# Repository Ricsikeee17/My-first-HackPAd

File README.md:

# SWITCHY

So this is my first ever project that gets a Github repository.

6 mechanical switches for macros

1 dedicated mode switch

Rotary encoder

OLED display for mode/status feedback

USB HID keyboard emulation

Built using Seeded XIAO RP2040.

## Features

Multiple macro modes (Mode 1 / Mode 2 / etc.)

OLED display shows:

Current mode

Encoder status

Custom labels (optional)

Rotary encoder:

Volume control

Fully programmable macros

## PCB

Here's a screenshot of the schematic:

The PCB:

## CAD Model
The case is made out 3 parts and it just only has parts that you could print.
It fits together using 4 M3 heatset inserts and bolts.

## BOM:
Here should be everything you need to make this hackpad

- 7x MX Switches
- 4x DSA Keycaps
- 4x M3x5x4 Heatset inserts
- 4x M3x16mm SHCS Bolts
- 7x 1N4148 DO-35 Diodes.
- 3x SK6812 MINI-E LEDs
- 1x 0.91" 128x32 OLED Display
- 1x EC11 Rotary Encoder
- 1x XIAO RP2040
- 1x Case (3 printed parts)

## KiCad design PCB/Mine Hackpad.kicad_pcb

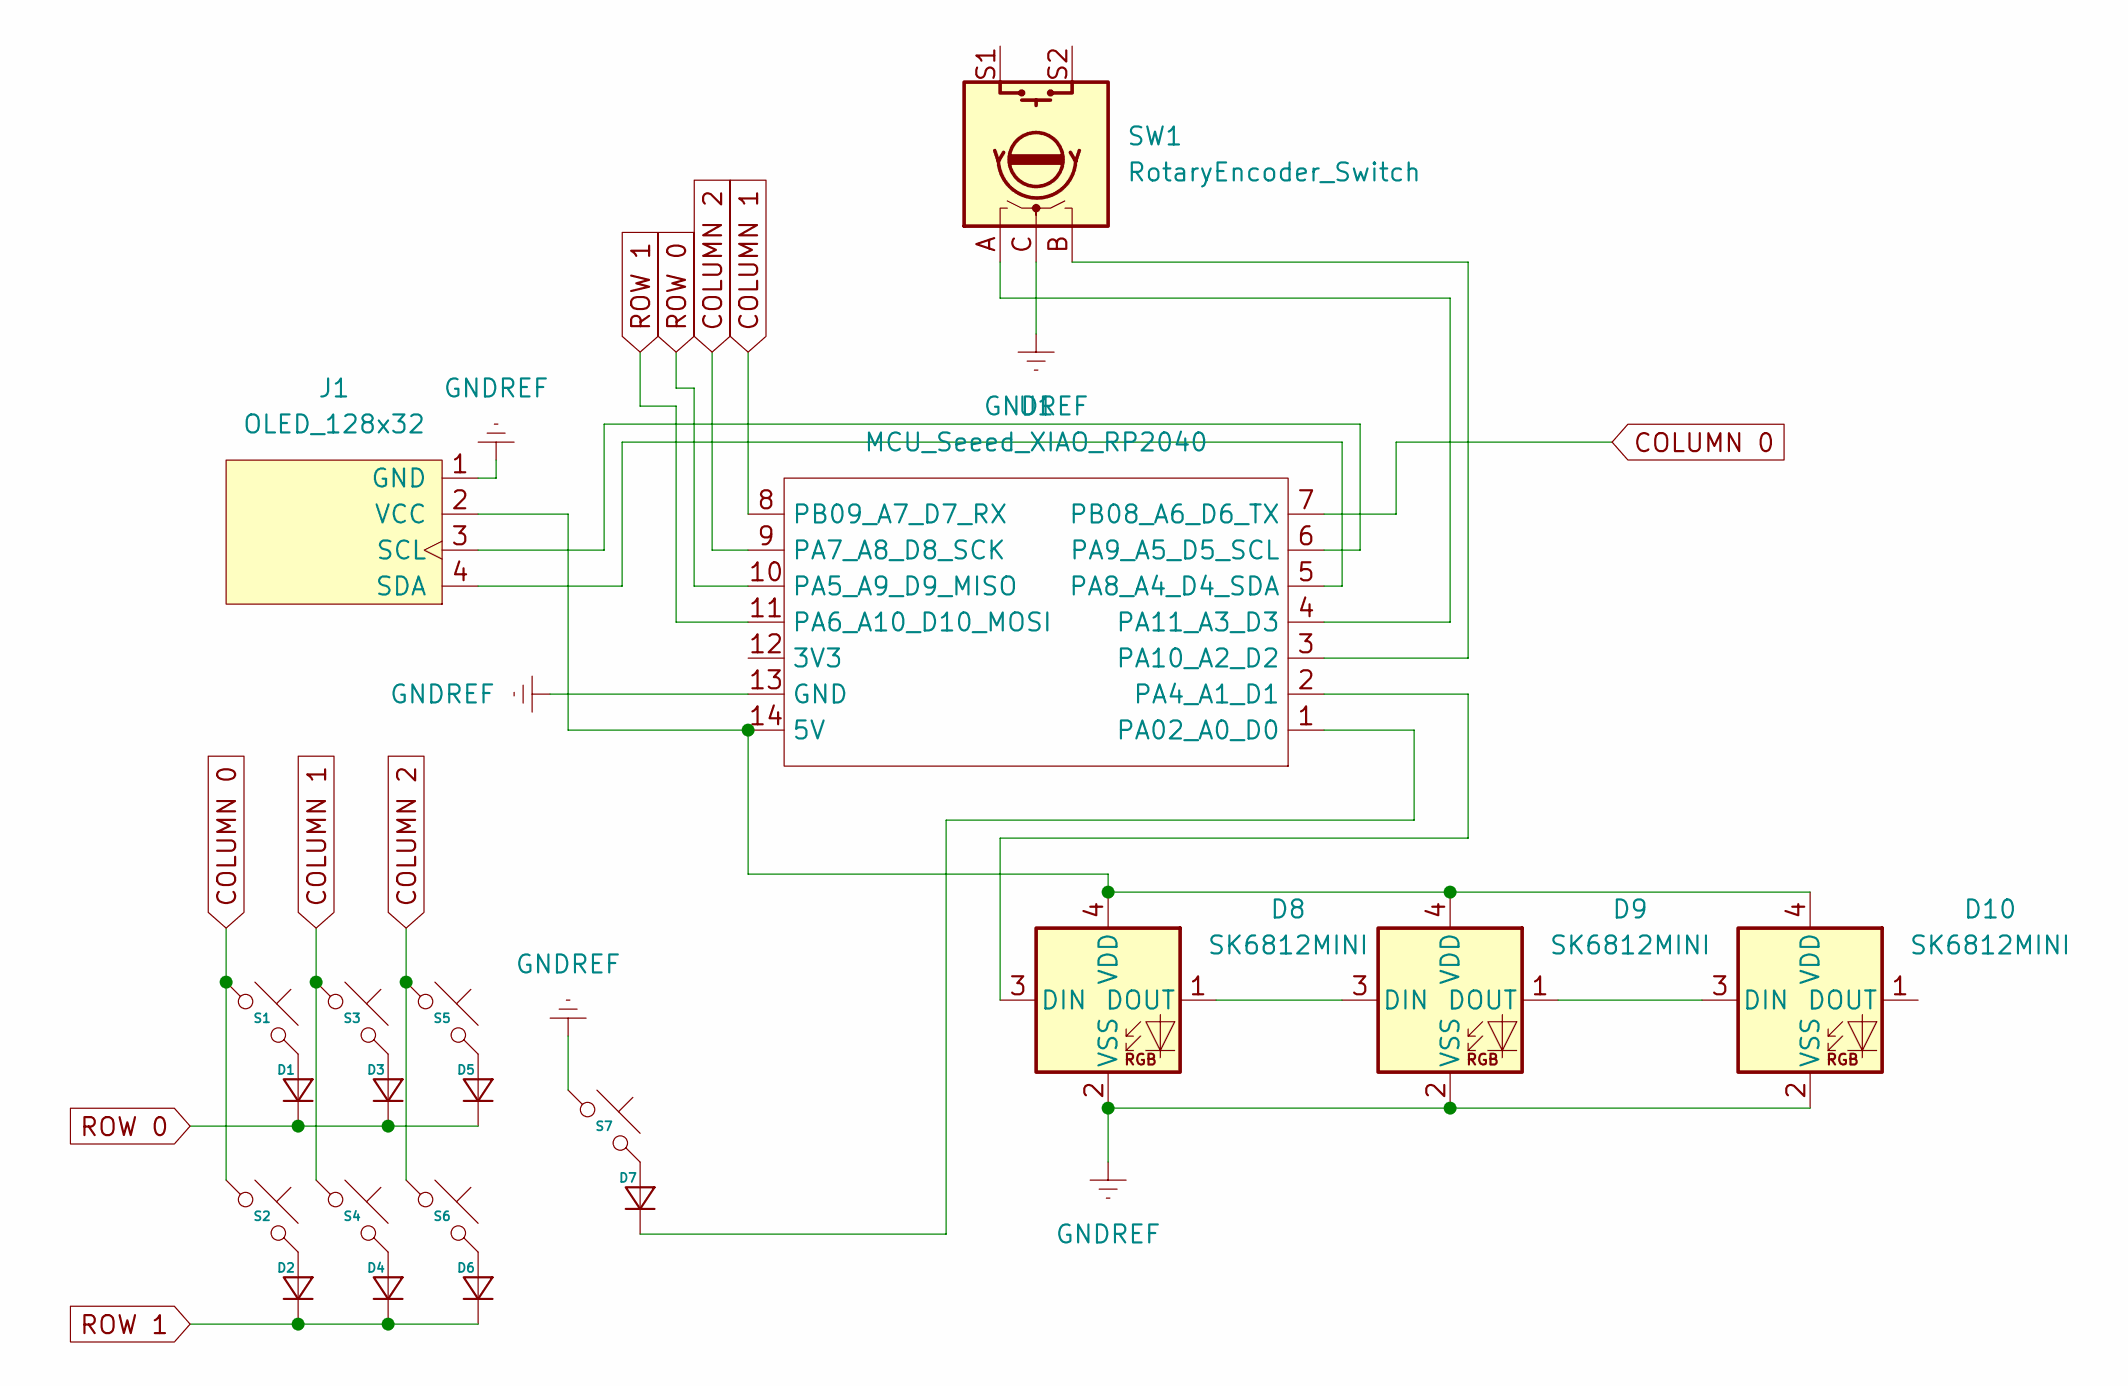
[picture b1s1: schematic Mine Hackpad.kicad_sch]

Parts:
D1, D2, D3, D4, D5, D6, D7: Diode_DO-35
D8, D9, D10: SK6812MINI; LED_SK6812MINI
J1: OLED_128x32
S1, S2, S3, S4, S5, S6, S7: MX_PCB_1.00u
SW1: RotaryEncoder_Switch; RotaryEncoder_Alps_EC11E-Switch_Vertical_H20mm
U1: MCU_Seeed_XIAO_RP2040; Seeed_XIAO_RP2040

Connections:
COLUMN 0: S1.1, S2.1, U1.7 (PB08_A6_D6_TX)
COLUMN 1: S3.1, S4.1, U1.8 (PB09_A7_D7_RX)
COLUMN 2: S5.1, S6.1, U1.9 (PA7_A8_D8_SCK)
GNDREF: D8.2 (VSS), D9.2 (VSS), D10.2 (VSS), J1.1 (GND), S7.1, SW1.C, U1.13 (GND)
unnamed: D1.2 (A), S1.2
unnamed: D2.2 (A), S2.2
unnamed: D3.2 (A), S3.2
unnamed: D4.2 (A), S4.2
unnamed: D5.2 (A), S5.2
unnamed: D6.2 (A), S6.2
unnamed: D7.2 (A), S7.2
unnamed: D7.1 (K), U1.1 (PA02_A0_D0)
unnamed: D8.3 (DIN), U1.2 (PA4_A1_D1)
unnamed: D8.1 (DOUT), D9.3 (DIN)
unnamed: D9.1 (DOUT), D10.3 (DIN)
unnamed: D8.4 (VDD), D9.4 (VDD), D10.4 (VDD), J1.2 (VCC), U1.14 (5V)
unnamed: J1.3 (SCL), U1.6 (PA9_A5_D5_SCL)
unnamed: J1.4 (SDA), U1.5 (PA8_A4_D4_SDA)
unnamed: SW1.B, U1.3 (PA10_A2_D2)
unnamed: SW1.A, U1.4 (PA11_A3_D3)
ROW 0: D1.1 (K), D3.1 (K), D5.1 (K), U1.10 (PA5_A9_D9_MISO)
ROW 1: D2.1 (K), D4.1 (K), D6.1 (K), U1.11 (PA6_A10_D10_MOSI)

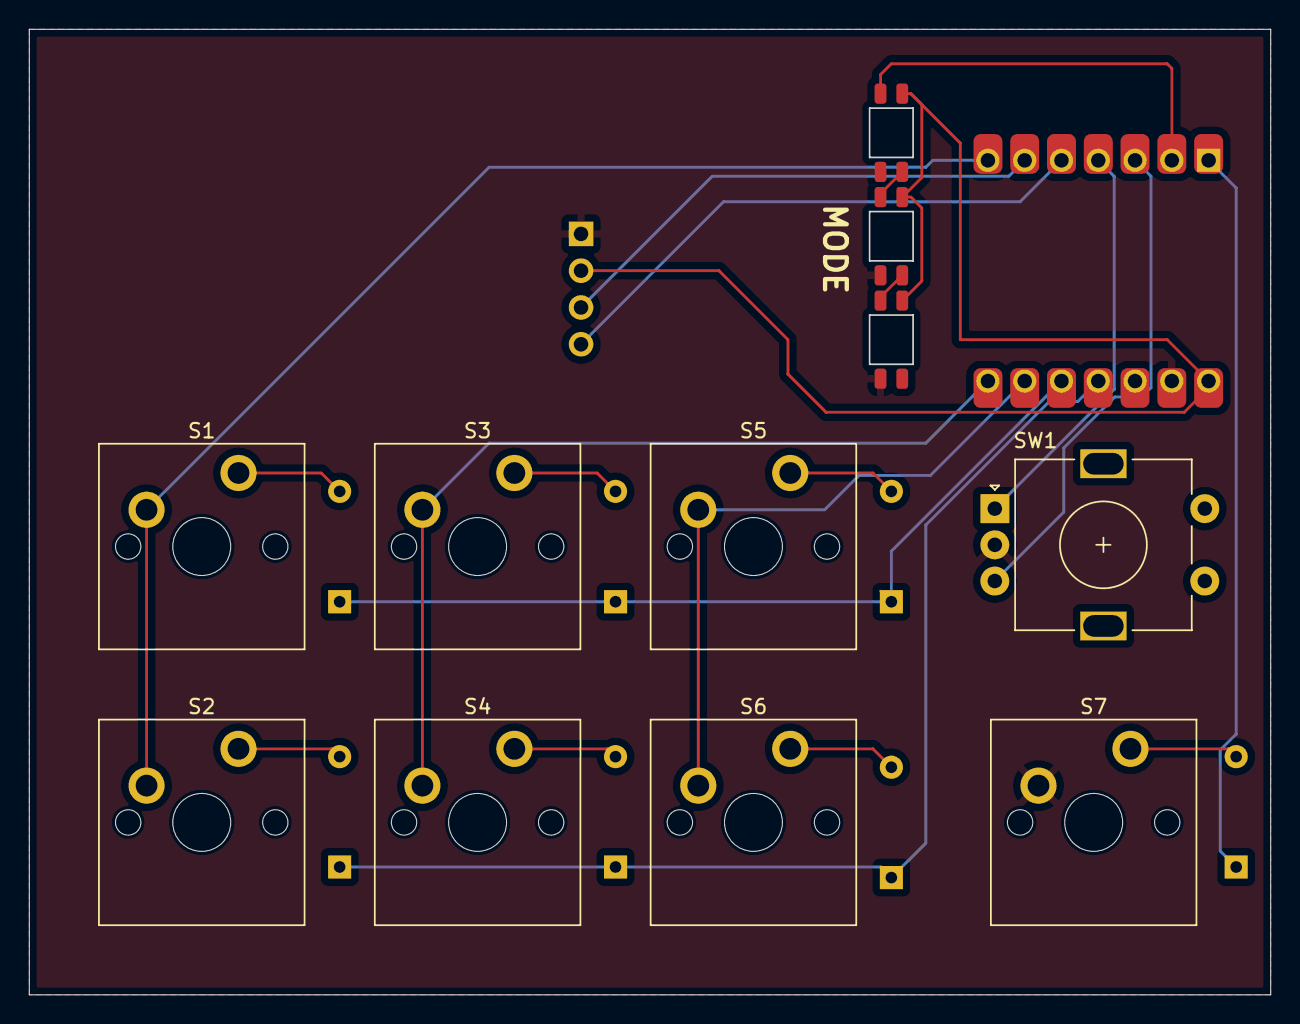
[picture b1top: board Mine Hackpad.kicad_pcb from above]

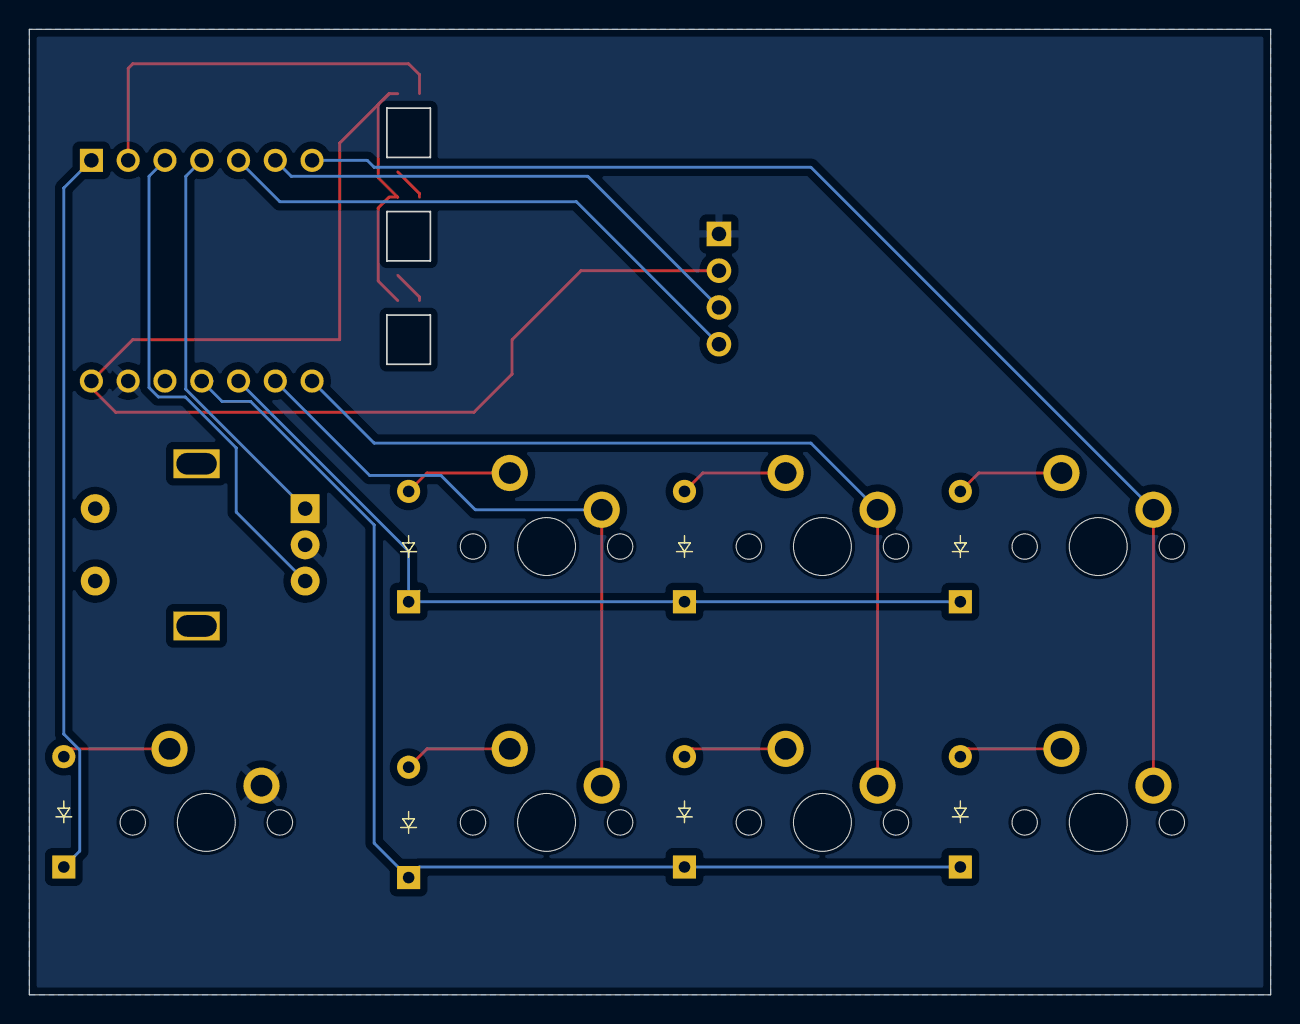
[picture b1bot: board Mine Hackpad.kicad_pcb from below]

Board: 2 copper layers, 85.7 x 66.6 mm, 20 parts (7 on the bottom side), 22 nets.

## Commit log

2026-02-27 Add files via upload
    This is the PCB with the components.
2026-02-27 Create 3DModel
2026-03-01 README.md
